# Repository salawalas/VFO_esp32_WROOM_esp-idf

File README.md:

# ESP32 VFO z generatorem Si5351A

Sterownik VFO zbudowany na ESP32-WROOM-32 i syntezerze Si5351A. Projekt generuje przestrajany sygnal w zakresie od 100 kHz do 225 MHz, pokazuje czestotliwosc na kolorowym wyswietlaczu TFT oraz udostepnia wygodna obsluge przez enkoder i piec przyciskow.

Repozytorium zawiera firmware ESP-IDF/PlatformIO oraz projekt PCB i schemat w KiCad.

## Najwazniejsze funkcje

- Zakres VFO: `100 kHz .. 225 MHz`.
- Syntezer Si5351A sterowany przez I2C 400 kHz.
- Wyjscia Si5351:
  - `CLK0` - glowny sygnal LO/VFO,
  - `CLK1` - nosna I,
  - `CLK2` - nosna Q, przesunieta wzgledem I.
- Kolorowy wyswietlacz ST7735 1.8", framebuffer `160 x 128 px`.
- Analogowa tarcza VFO oraz cyfrowy odczyt czestotliwosci.
- Enkoder kwadraturowy PCNT z dynamicznym przyspieszaniem strojenia.
- Kroki strojenia: `10 Hz`, `100 Hz`, `1 kHz`, `10 kHz`, `100 kHz`, `1 MHz`.
- Dziesiec komorek pamieci `M0..M9`.
- Autozapis ostatniej czestotliwosci do NVS po okresie bezczynnosci.
- Menu pasm z gotowymi czestotliwosciami startowymi.
- Blokada strojenia `LOCK`.
- Kalibracja czestotliwosci kwarcu Si5351 w zakresie `-5000..+5000 Hz`.
- Regulacja jasnosci podswietlenia PWM.
- Oddzielne srodowiska PlatformIO: `esp32_release` i `esp32_debug`.

## Sprzet

Glownymi elementami ukladu sa:

- ESP32-WROOM-32,
- modul Si5351A,
- wyswietlacz TFT 1.8" ze sterownikiem ST7735,
- enkoder obrotowy z przyciskiem,
- 5 przyciskow tact switch,
- podswietlenie wyswietlacza sterowane PWM,
- plytka PCB zaprojektowana w KiCad.

Pliki KiCad sa w katalogu `Kicad files/`.

## Polaczenia GPIO

| Funkcja | GPIO |
| --- | ---: |
| Enkoder A | 17 |
| Enkoder B | 16 |
| Przycisk enkodera SW | 34 |
| STEP_DN | 26 |
| STEP_UP | 27 |
| MEM | 25 |
| SAVE | 32 |
| BAND | 33 |
| Si5351 SDA | 21 |
| Si5351 SCL | 22 |
| ST7735 SCLK | 18 |
| ST7735 MOSI | 23 |
| ST7735 CS | 5 |
| ST7735 DC | 2 |
| ST7735 RST | 15 |
| Podswietlenie TFT | 4 |

Przyciski sa aktywne stanem niskim. W tej konstrukcji zewnetrzne rezystory pull-up sa wymagane dla GPIO16, GPIO17, GPIO33 i GPIO34. Na plytce zastosowano 4.7 kOhm, ale praktyczny zakres to ok. 2.2 kOhm .. 10 kOhm.

## Ekran

Normalny widok VFO pokazuje:

- analogowa tarcze strojenia,
- cyfrowa czestotliwosc generowana,
- aktywny krok strojenia,
- aktywny bank pamieci `VFO` albo `M1..M9`,
- graficzne overlaye dla operacji `SAVE`, `LOAD`, `LOCK`, menu pasm, jasnosci i kalibracji.

W trybie `LOCK` czestotliwosc pozostaje widoczna, a na ekranie pojawia sie duzy symbol klodki oraz napis `LOCK` na dole.

## Obsluga

### Enkoder

| Akcja | Efekt |
| --- | --- |
| Obrot w trybie VFO | Zmiana czestotliwosci wedlug aktywnego kroku |
| Szybki obrot | Automatyczne przyspieszenie strojenia `x10`, `x100`, `x1000` |
| Krotkie nacisniecie SW | Otwarcie menu pasm lub zatwierdzenie wyboru pasma |
| Dlugie nacisniecie SW | Zmiana kierunku pracy enkodera |
| Obrot w menu BAND | Przewijanie listy pasm |
| Obrot w XTAL CAL | Zmiana korekty kwarcu |
| Obrot w BRIGHTNESS | Zmiana jasnosci podswietlenia |

### Przyciski

| Przycisk | Krotkie nacisniecie | Dlugie nacisniecie |
| --- | --- | --- |
| STEP_DN | Mniejszy krok strojenia | - |
| STEP_UP | Wiekszy krok strojenia | - |
| MEM | Nastepny bank pamieci / YES w dialogu / SAVE w ekranach ustawien | Wczytanie czestotliwosci z aktywnego banku |
| SAVE | NO/CANCEL w dialogach | Otwarcie dialogu zapisu do aktywnego banku |
| BAND | Ekran regulacji jasnosci | Kalibracja kwarcu XTAL |
| STEP_DN + STEP_UP | `LOCK` po przytrzymaniu ok. 1 s | `LOCK` po przytrzymaniu ok. 1 s |

W trybie `LOCK` zmiana czestotliwosci i kroku jest blokowana. Odblokowanie odbywa sie ta sama kombinacja `STEP_DN + STEP_UP`.

## Pamiec i pasma

Firmware przechowuje parametry w NVS:

- ostatnia czestotliwosc,
- 10 komorek pamieci `M0..M9`,
- ostatni krok strojenia,
- korekta kwarcu Si5351,
- jasnosc wyswietlacza,
- ostatnio uzywany bank.

Domyslne komorki pamieci:

| Bank | Czestotliwosc |
| --- | ---: |
| M0 | 14.230 MHz |
| M1 | 3.730 MHz |
| M2 | 3.8531 MHz |
| M3 | 5.450 MHz |
| M4 | 5.505 MHz |
| M5 | 6.070 MHz |
| M6 | 7.130 MHz |
| M7 | 7.8781 MHz |
| M8 | 8.957 MHz |
| M9 | 10.100 MHz |

Menu pasm zawiera:

`30m`, `20m`, `17m`, `15m`, `12m`, `10m`, `6m` oraz `FM 100 MHz`.

## Tryby ekranowe

- `VFO` - normalna praca i strojenie.
- `SAVE TO Mx?` - potwierdzenie zapisu aktualnej czestotliwosci do pamieci.
- `SAVED` - komunikat po zapisie.
- `LOAD` - komunikat po wczytaniu pamieci.
- `SELECT BAND` - wybor pasma lub preset FM.
- `BRIGHTNESS` - regulacja jasnosci podswietlenia.
- `XTAL CALIBRATION` - korekta czestotliwosci referencyjnej Si5351.
- `LOCK` - blokada przypadkowej zmiany czestotliwosci.

## Budowanie

Projekt jest przygotowany pod PlatformIO z frameworkiem ESP-IDF.

Domyslnym srodowiskiem jest release:

```powershell
pio run
```

Jawny build release:

```powershell
pio run -e esp32_release
```

Build debug:

```powershell
pio run -e esp32_debug
```

Wgrywanie:

```powershell
pio run -e esp32_release -t upload
```

Monitor portu szeregowego:

```powershell
pio device monitor
```

Domyslny port uploadu w `platformio.ini` to `COM42`.

## Konfiguracja buildow

`platformio.ini` definiuje dwa warianty:

- `esp32_release` - normalny build firmware,
- `esp32_debug` - build debug z wyzszym poziomem logow.

Wspolne ustawienia ESP-IDF sa w `sdkconfig.defaults`. Dodatkowe ustawienia debug sa w `sdkconfig.debug.defaults`. Pelne pliki `sdkconfig.esp32_*` sa generowane przez PlatformIO lokalnie i sa ignorowane przez git.

## Struktura projektu

| Sciezka | Opis |
| --- | --- |
| `src/main.c` | Inicjalizacja systemu, zadanie wyswietlacza |
| `src/si5351.c` | Sterownik i obliczenia rejestrow Si5351 |
| `src/display.c` | Sterownik ST7735 i transfer DMA |
| `src/graph.c` | Framebuffer RGB i prymitywy graficzne |
| `src/dial.c` | Analogowa tarcza VFO |
| `src/encoder.c` | Obsluga enkodera PCNT |
| `src/buttons.c` | Obsluga przyciskow i trybow |
| `src/nvs_storage.c` | Pamiec NVS i autozapis |
| `src/ui_overlay.c` | Overlaye graficzne i menu |
| `include/config.h` | Glowne stale konfiguracyjne |
| `Kicad files/` | Projekt PCB i schemat |

## Uwagi

Projekt jest przeznaczony do pracy jako eksperymentalny generator/VFO. Przy podlaczaniu do torow radiowych nalezy zadbac o odpowiednie poziomy sygnalu, filtracje harmonicznych, ekranowanie i zgodnosc z lokalnymi przepisami dotyczacymi emisji radiowych.

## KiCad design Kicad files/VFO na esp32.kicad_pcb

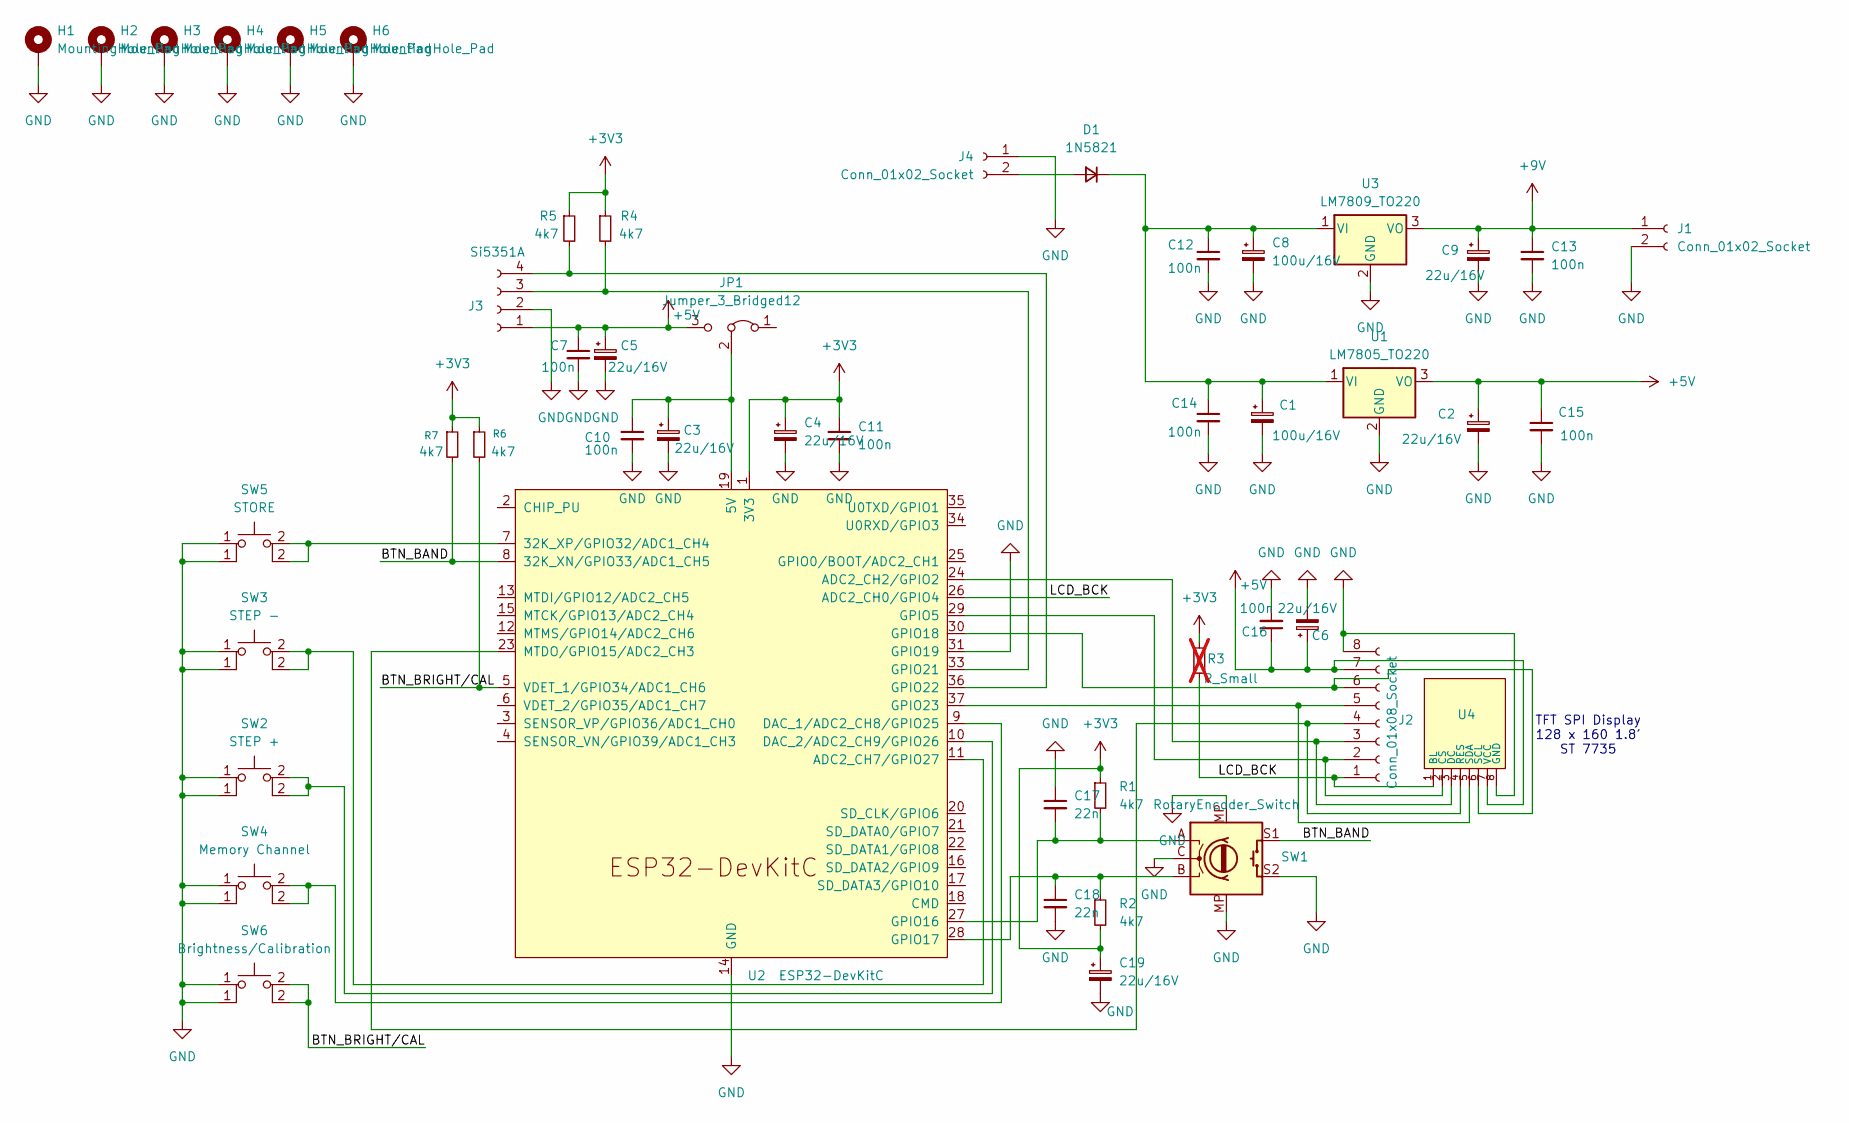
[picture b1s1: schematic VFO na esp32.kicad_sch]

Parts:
C1, C8: 100u/16V; CP_Radial_D8.0mm_P3.50mm
C2, C3, C4, C5, C6, C9, C19: 22u/16V; CP_Radial_Tantal_D5.0mm_P5.00mm
C7, C10, C11, C12, C13, C14, C15, C16: 100n; C_0805_2012Metric_Pad1.18x1.45mm_HandSolder
C17, C18: 22n; C_Axial_L5.1mm_D3.1mm_P10.00mm_Horizontal
D1: 1N5821; D_DO-15_P10.16mm_Horizontal
H1, H2, H3, H4, H5, H6: MountingHole_Pad; MountingHole_2.7mm_M2.5_DIN965_Pad_TopBottom
J1, J4: Conn_01x02_Socket; JST_EH_S2B-EH_1x02_P2.50mm_Horizontal
J2: Conn_01x08_Socket; PinSocket_1x08_P2.54mm_Vertical
J3: Si5351A; JST_PH_B4B-PH-K_1x04_P2.00mm_Vertical
JP1: Jumper_3_Bridged12; PinHeader_1x03_P2.54mm_Vertical
R1, R2: 4k7; R_Axial_DIN0207_L6.3mm_D2.5mm_P10.16mm_Horizontal
R3: R_Small; R_Axial_DIN0207_L6.3mm_D2.5mm_P10.16mm_Horizontal; not fitted
R4, R5: 4k7; R_0805_2012Metric_Pad1.20x1.40mm_HandSolder
R6, R7: 4k7; R_1206_3216Metric
SW1: RotaryEncoder_Switch; RotaryEncoder_Alps_EC11E-Switch_Vertical_H20mm
SW2: STEP +; SW_PUSH_6mm_H5mm
SW3: STEP -; SW_PUSH_6mm_H5mm
SW4: Memory Channel; SW_PUSH_6mm_H5mm
SW5: STORE; SW_PUSH_6mm_H5mm
SW6: Brightness/Calibration; SW_PUSH_6mm_H5mm
U1: LM7805_TO220; TO-220F-3_Horizontal_TabDown
U2: ESP32-DevKitC
U3: LM7809_TO220; TO-220F-3_Horizontal_TabDown
U4: TFT_SPI_1.8inch_128x160

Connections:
+3V3: C4.1, C11.1, C19.1, R1.1, R2.2, R3.2, R4.1, R5.1, R6.1, R7.1, U2.1 (3V3)
+5V: C2.1, C5.1, C6.1, C7.1, C15.1, C16.1, J2.7, J3.1, JP1.3 (B), U1.3 (VO), U4.7 (VCC)
+9V: C9.1, C13.1, J1.1, U3.3 (VO)
/BTN_BAND: R7.2, SW1.S1, U2.8 (32K_XN/GPIO33/ADC1_CH5)
/BTN_BRIGHT/CAL: R6.2, SW6.2, U2.5 (VDET_1/GPIO34/ADC1_CH6)
/LCD_BCK: J2.1, R3.1, U2.26 (ADC2_CH0/GPIO4), U4.1 (BL)
GND: C1.2, C2.2, C3.2, C4.2, C5.2, C6.2, C7.2, C8.2, C9.2, C10.2, C11.2, C12.2, C13.2, C14.2, C15.2, C16.2, C17.1, C18.2, C19.2, H1.1 (1_1), H2.1 (1_1), H3.1 (1_1), H4.1 (1_1), H5.1 (1_1), H6.1 (1_1), J1.2, J2.8, J3.2, J4.1, SW1.C, SW1.MP, SW1.S2, SW2.1, SW3.1, SW4.1, SW5.1, SW6.1, U1.2 (GND), U2.14 (GND), U2.31 (GPIO19), U2.32 (GND), U2.38 (GND), U3.2 (GND), U4.8 (GND)
unnamed: D1.2 (A), J4.2
unnamed: C1.1, C8.1, C12.1, C14.1, D1.1 (K), U1.1 (VI), U3.1 (VI)
unnamed: J2.2, U2.29 (GPIO5), U4.2 (CS)
unnamed: J2.3, U2.24 (ADC2_CH2/GPIO2), U4.3 (DC)
unnamed: J2.4, U2.23 (MTDO/GPIO15/ADC2_CH3), U4.4 (RES)
unnamed: J2.5, U2.37 (GPIO23), U4.5 (SDA)
unnamed: J2.6, U2.30 (GPIO18), U4.6 (SCL)
unnamed: J3.3, R4.2, U2.33 (GPIO21)
unnamed: J3.4, R5.2, U2.36 (GPIO22)
unnamed: C3.1, C10.1, JP1.2 (C), U2.19 (5V)
unnamed: SW5.2, U2.7 (32K_XP/GPIO32/ADC1_CH4)
unnamed: SW3.2, U2.11 (ADC2_CH7/GPIO27)
unnamed: SW4.2, U2.9 (DAC_1/ADC2_CH8/GPIO25)
unnamed: SW2.2, U2.10 (DAC_2/ADC2_CH9/GPIO26)
unnamed: C17.2, R1.2, SW1.A, U2.27 (GPIO16)
unnamed: C18.1, R2.1, SW1.B, U2.28 (GPIO17)

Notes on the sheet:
TFT SPI Display 128 x 160 1.8' ST 7735

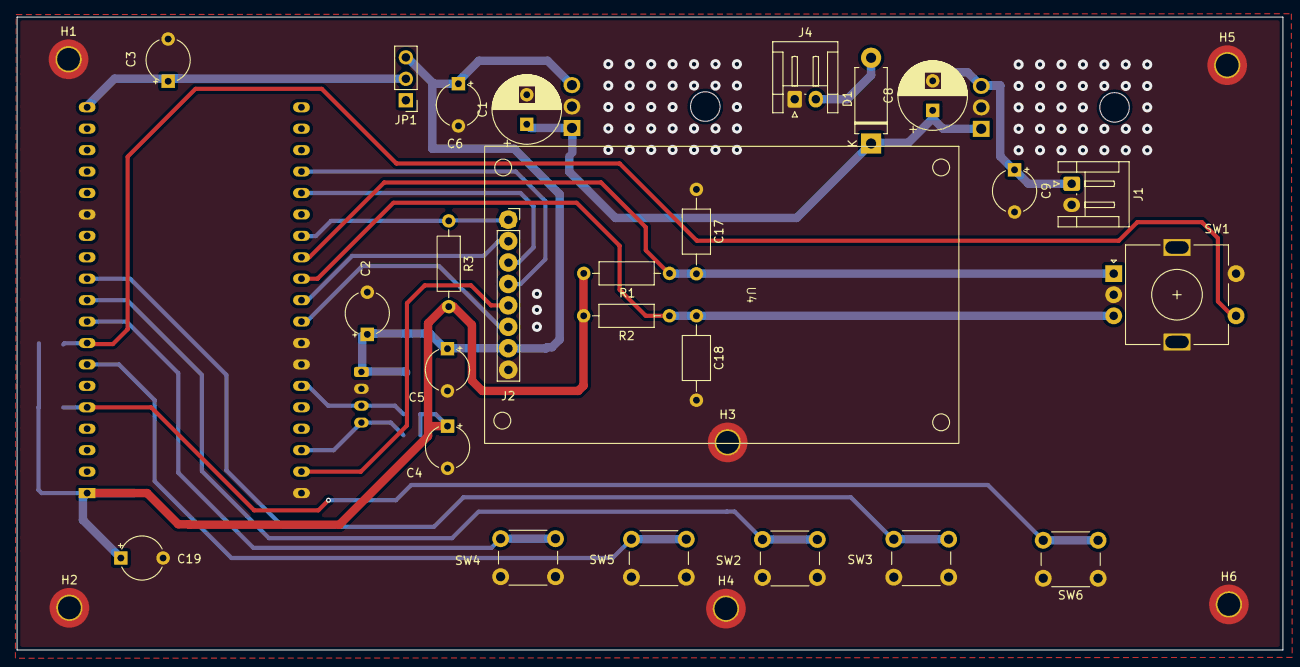
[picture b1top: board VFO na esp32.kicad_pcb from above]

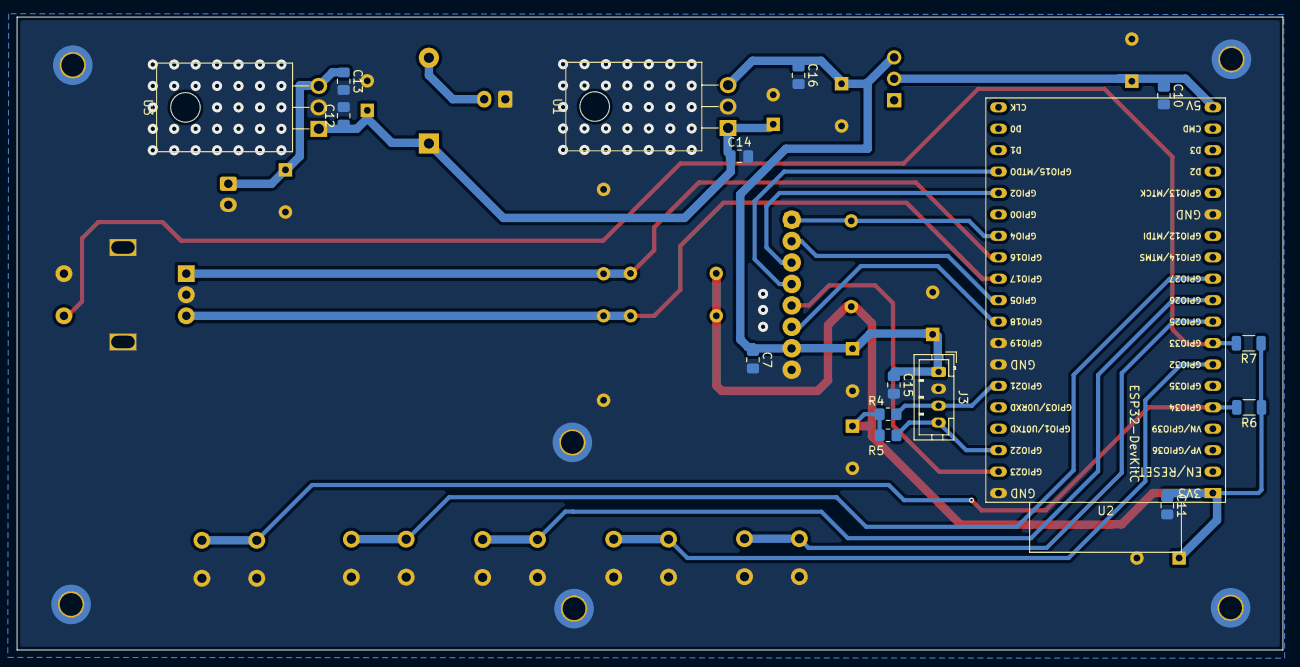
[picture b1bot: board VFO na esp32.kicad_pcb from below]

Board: 2 copper layers, 150.0 x 75.0 mm, 48 parts (16 on the bottom side), 23 nets.

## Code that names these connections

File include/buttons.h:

/*===========================================================================
 *  buttons.h — Przyciski tact switch (ESP-IDF 5.x)
 *
 *  Przyciski (active LOW, INPUT_PULLUP):
 *    BTN_STEP_DN (GPIO27) — krok w dol
 *    BTN_STEP_UP (GPIO26) — krok w gore
 *    BTN_MEM     (GPIO25) — pamiec / YES w dialogu zapisu
 *    BTN_SAVE    (GPIO32) — zapis / NO w dialogu
 *    BTN_BAND    (GPIO33) — menu wyboru pasma (5. przycisk)
 *
 *  Logika czasowa:
 *    Krotkie nacisniecie (<500ms): akcja podstawowa
 *    Dlugie  (>=1000ms):           akcja alternatywna
 *    LOCK: BTN_STEP_DN + BTN_STEP_UP trzymane >= 1s jednoczesnie
 *===========================================================================*/
#pragma once
#include "esp_err.h"
#include <stdbool.h>

/* GPIO 5. przycisku BAND — zmien gdy znany */
#define BTN_BAND    33    /* wbudowany pull-up dostepny */

esp_err_t buttons_init(void);
void      buttons_task(void *arg);

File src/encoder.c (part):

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
    /* --- Kanal 0: pulse=A(17), ctrl=B(16) --- */
    pcnt_chan_config_t ch0_cfg = {
        .edge_gpio_num  = ENC_PIN_A,   /* GPIO17 */
        .level_gpio_num = ENC_PIN_B,   /* GPIO16 */
    };
    pcnt_channel_handle_t ch0 = NULL;
    err = pcnt_new_channel(s_pcnt_unit, &ch0_cfg, &ch0);
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
    /* --- Kanal 1: pulse=B(16), ctrl=A(17) --- */
    pcnt_chan_config_t ch1_cfg = {
        .edge_gpio_num  = ENC_PIN_B,   /* GPIO16 */
        .level_gpio_num = ENC_PIN_A,   /* GPIO17 */
    };
    pcnt_channel_handle_t ch1 = NULL;
    err = pcnt_new_channel(s_pcnt_unit, &ch1_cfg, &ch1);
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    /* --- GPIO dla przycisku SW enkodera ---
     * ENC_PIN_SW=34 jest input-only — nie mozna ustawic pull-up programowo.
     * Wymaga zewnetrznego rezystora 10k do VCC.
     * Jesli uzywasz GPIO33 lub innego z pull-up: zmien na GPIO_PULLUP_ENABLE */
    gpio_config_t sw_cfg = {
        .pin_bit_mask = (1ULL << ENC_PIN_SW),
        .mode         = GPIO_MODE_INPUT,
        .pull_up_en   = GPIO_PULLUP_DISABLE,   /* brak dla GPIO34 */
        .pull_down_en = GPIO_PULLDOWN_DISABLE,
        .intr_type    = GPIO_INTR_DISABLE,
    };
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
        /* ----------------------------------------------------------------
         *  4. Przycisk SW enkodera
         *     GPIO34 jest active LOW (przycisk zwiera do GND)
         * -------------------------------------------------------------- */
        bool sw_now = gpio_get_level(ENC_PIN_SW);   /* LOW = wcisniety */

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
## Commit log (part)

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2026-04-01 zmiany kalibracja Si5351, poprawione wyjście CLK0
2026-04-01 zmiany kalibracja, zmiana działania buttonów
2026-04-01 zmiany regulacja jasności, naprawa kalibracji
2026-04-02 zmiana kierunku obracania tarcz
2026-04-02 zmiana offset
2026-04-02 Create workflows
2026-04-02 add github build workflow
2026-04-02 zmiana zawartości pliku build.yml dla esp-idf
2026-04-02 zmiana yml na platformio
2026-04-02 zmiana dla cashowania toolchainu
2026-04-02 Zmiana offsetu wyświetlacza.
2026-04-02 Zmiana offsetu wyświetlacza col=2 row=1
2026-04-02 Workflow dla vfo-pio
2026-04-02 fix CI python version
2026-04-02 fix CI workflow
2026-04-02 Zmiana splash screen.
2026-04-02 Zmiana werski commita.
2026-04-03 Zmiana przesunięcie tekstu w splash screen.
2026-04-03 Create LICENSE
2026-04-03 Zmiana pliku build.yml
2026-04-03 Zmiana pilku build.yml, nowe wersje otagowania
2026-04-03 Zmiana w pliku buil, zbudowanie binarek
2026-04-04 Zumiany w optymalizacji kompilacji -O2
2026-04-05 Dodanie env_devel, fix do pliku build.yml
2026-04-05 Fix dla build.yml
2026-04-05 Dodanie cache dla Platformio i pip w build.yml.
2026-04-06 Zmiany, dodanie środowisk : release i debug
2026-04-06 Fiix build.yml
2026-04-06 Fix build.yml+
2026-04-06 lstest fix
2026-04-06 Latest ficx buil.yml.
2026-04-06 Last fix.
2026-04-06 Usunięcie workflow/build.yml.
2026-04-06 Dodanie plików w Kicad 10.
2026-04-08 Zmiana , dodanie settings.json.
2026-04-13 Zmiana w Cmakelist.txt pod esp-idf.
2026-04-14 Zmianw wyglądzie Splash screen, dodanie wersji commit.
2026-05-17 Poprawki w kodzie wyświetlanych subekranów, poprawki w konfiguracji sdkconfig.
2026-05-17 Dodano nowy plik README.md, poprawki w plikach projektu pcb w KICAD10.
2026-06-14 Zmiany w kalibracji kwarcu, zmiana głównej nosnej na CLK0 w Si5351.
2026-06-14 Zmiana wersji firmware..
